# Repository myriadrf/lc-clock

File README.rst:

LibreCellular Reference Clock Designs
=====================================

.. image:: https://raw.githubusercontent.com/myriadrf/lc-clock/main/images/CSAD10_0p2_PCB_1_1280w.jpg
   :alt: CSAD10 prototype.

This repository contains the LibreCellular reference clock PCB (KiCAD) designs.

CSAD10
------

Performs clock shaping and distribution. Takes a sine or square wave as input and provides provides ten square wave outputs.

For further details see the `LibreCellular Documentation`_.

CSAD2 (WIP) 
-----------

Performs clock shaping and distribution. Takes a sine or square wave as input and provides provides two square wave outputs.

**Warning: do not build! This is a work in progress and the current design does not provide sufficient output level.**

Licence
-------

LibreCelluar Reference Clock Designs is copyright 2023 AB Open Ltd and provided under the Solderpad Hardware License v2.1.

.. _LibreCellular Documentation: https://librecellular.org/developer/hardware/ci/csad10.html

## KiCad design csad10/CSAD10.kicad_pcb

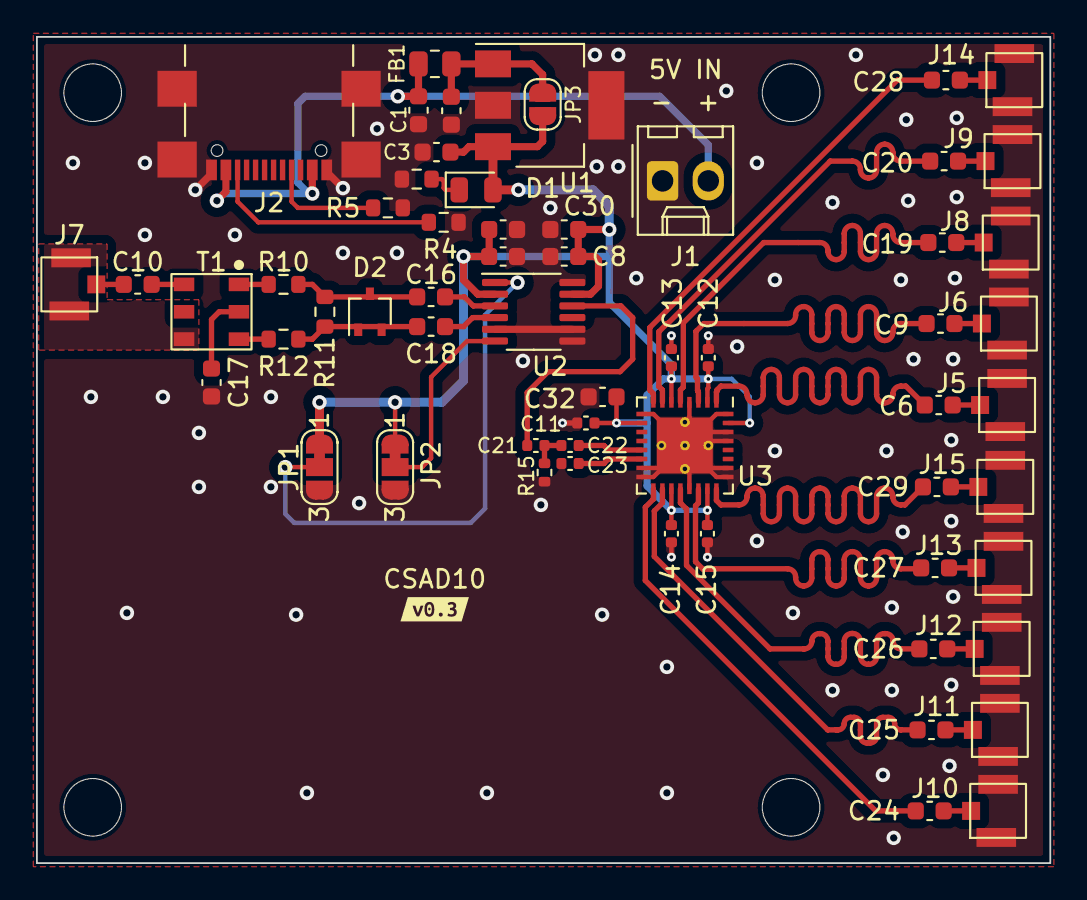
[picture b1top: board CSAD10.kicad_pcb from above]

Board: 4 copper layers, 56.3 x 45.9 mm, 65 parts (0 on the bottom side), 43 nets.

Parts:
C1, C2, C30, C31, C32: 1uF; C_0603_1608Metric
C3: 4.7uF; C_0603_1608Metric
C6, C7, C8, C9, C10, C16, C17, C18, C19, C20, C24, C25, C26, C27, C28, C29: 0.1uF; C_0603_1608Metric
C11, C12, C13, C14, C15: 100pF; C_0402_1005Metric
C21, C22, C23: 0.1uF; C_0402_1005Metric
D1: 150080GS75000; LED_0805_2012Metric
D2: MA4E133B1-1146T; SOT-323_SC-70
FB1: 60R @ 100MHz; R_0805_2012Metric
H1, H2, H3, H4: MountingHole; MountingHole_3.2mm_M3_ISO7380
J1: 22-23-2021; Molex_KK-254_AE-6410-02A_1x02_P2.54mm_Vertical
J2: USB4110-GF-A; USB_C_Receptacle_GCT_USB4110-xx-A_16P_TopMnt_Horizontal
J5, J6, J7, J8, J9, J10, J11, J12, J13, J14, J15: U.FL-R-SMT(01); Connector_RF_Hirose_U.FL-R-SMT(01)
JP1, JP2: SolderJumper_3_Bridged12; SolderJumper-3_P1.3mm_Bridged12_RoundedPad1.0x1.5mm_NumberL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
JP3: SolderJumper_2_Open; SolderJumper-2_P1.3mm_Open_RoundedPad1.0x1.5mm
R1: 680R; R_0603_1608Metric
R4, R5: 5K1; R_0603_1608Metric
R10, R12: 100R; R_0603_1608Metric
R11: 604R; R_0603_1608Metric
R15: 50R; R_0402_1005Metric
T1: WBC16-1T; Transformer_Coilcraft_WBC_Series
U1: AP7361C-33E; SOT-223-3_TabPin2
U2: LTC6957IMS-3; MSOP-12_3x4mm_P0.65mm
U3: LMK00101; WQFN-32-1EP_5x5mm_P0.5mm_EP3.1x3.1mm_ThermalVias
kibuzzard-6492A46E: G***; kibuzzard-6492A46E

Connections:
+3.3V: C3.2, C7.2, C8.2, C11.2, C12.2, C13.2, C14.2, C15.2, C30.2, C31.2, C32.2, D1.2 (A), JP1.1 (A), JP2.1 (A), JP3.1 (A), U1.3 (VO), U2.2 (V+), U2.11 (VDD), U3.2 (VddoA), U3.6 (VddoA), U3.10 (Vdd), U3.19 (VddoB), U3.23 (VddoB), U3.31 (OE)
Earth: J7.2 (Ext), T1.4 (AB)
GND: C1.1, C2.1, C3.1, C7.1, C8.1, C11.1, C12.1, C13.1, C14.1, C15.1, C17.2, C23.2, C30.1, C31.1, C32.1, J1.1, J2.A1 (GND), J2.A12 (GND), J2.B1 (GND), J2.B12 (GND), J2.S1 (SHIELD), J5.2 (Ext), J6.2 (Ext), J8.2 (Ext), J9.2 (Ext), J10.2 (Ext), J11.2 (Ext), J12.2 (Ext), J13.2 (Ext), J14.2 (Ext), J15.2 (Ext), JP1.3 (B), JP2.3 (B), R1.2, R4.1, R5.1, R15.1, U1.2 (GND), U2.5 (GND), U2.7 (SD2), U2.8 (GNDOUT), U2.12 (SD1), U3.4 (GND), U3.9 (GND), U3.15 (GND), U3.16 (GND), U3.21 (GND), U3.25 (GND), U3.26 (GND), U3.29 (SEL1), U3.30 (SEL0), U3.32 (GND), U3.33 (EP)
unnamed: C18.1, D2.1 (K), D2.2 (K), R11.2, R12.2
unnamed: C21.1, C22.2, R15.2
unnamed: D1.1 (K), R1.1
unnamed: C16.1, D2.3 (A), R10.2, R11.1
unnamed: C1.2, FB1.1, J1.2, J2.A4 (VBUS), J2.A9 (VBUS), J2.B4 (VBUS), J2.B9 (VBUS)
unnamed: J2.A5 (CC1), R5.2
unnamed: J2.B5 (CC2), R4.2
unnamed: C6.1, J5.1 (In)
unnamed: C9.1, J6.1 (In)
unnamed: C10.1, J7.1 (In)
unnamed: C19.1, J8.1 (In)
unnamed: C20.1, J9.1 (In)
unnamed: C24.1, J10.1 (In)
unnamed: C25.1, J11.1 (In)
unnamed: C26.1, J12.1 (In)
unnamed: C27.1, J13.1 (In)
unnamed: C28.1, J14.1 (In)
unnamed: C29.1, J15.1 (In)
unnamed: JP1.2 (C), U2.1 (FILTA)
unnamed: JP2.2 (C), U2.6 (FILTB)
unnamed: C2.2, FB1.2, JP3.2 (B), U1.1 (VI)
unnamed: C10.2, T1.6 (AA)
unnamed: R12.1, T1.3 (SA)
unnamed: R10.1, T1.1 (SB)
unnamed: C17.1, T1.2 (SC)
unnamed: C16.2, U2.3 (IN+)
unnamed: C18.2, U2.4 (IN-)
unnamed: C21.2, U2.10 (OUT1)
unnamed: C22.1, U3.13 (CLKin0)
unnamed: C23.1, U3.14 (CLKin0*)
unnamed: C6.2, U3.1 (CLKout0)
unnamed: C9.2, U3.3 (CLKout1)
unnamed: C19.2, U3.5 (CLKout2)
unnamed: C20.2, U3.7 (CLKout3)
unnamed: C28.2, U3.8 (CLKout4)
unnamed: C24.2, U3.17 (CLKout5)
unnamed: C25.2, U3.18 (CLKout6)
unnamed: C26.2, U3.20 (CLKout7)
unnamed: C27.2, U3.22 (CLKout8)
unnamed: C29.2, U3.24 (CLKout9)

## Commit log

2023-08-11 Add CSAD2 & CSAD10
2024-01-13 Add README.
